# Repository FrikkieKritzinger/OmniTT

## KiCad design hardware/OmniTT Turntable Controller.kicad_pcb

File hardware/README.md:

# Hardware (KiCad 10)

KiCad project for the OmniTT controller: main board (`OmniTT Turntable Controller.kicad_pcb`),
the root schematic, and the two sub-sheets:

- `tt_control.kicad_sch`: button board (J5, ladder, shortcut buttons)
- `loconet_interface.kicad_sch`: LocoNet interface (J7, Q3, U5, R9 to R14), unpopulated in this revision

Open `OmniTT Turntable Controller.kicad_pro` in KiCad 10.

## External libraries

The design uses two custom libraries.

| Library nickname | Used for | Where it lives | Origin |
|---|---|---|---|
| `DFRobot` (symbol) and `library` (footprint) | DFRobot TB6612FNG motor driver module (U3) | In the repo: `libraries/DFRobot.kicad_sym` and `libraries/library.pretty/` | Designed by the author |
| `TTGO_T7_MINI32_V1.3` (symbol and footprint) | ESP32 D1 Mini (WROOM-32) module (U4) | Not in the repo | Downloaded footprint (SnapEDA basis), modified by the author |

`sym-lib-table` and `fp-lib-table` point KiCad at the in-repo libraries using `${KIPRJMOD}`,
so the project resolves them without any global setup.

The TTGO library isn't in the repo. Install it in KiCad from your own copy before opening
the project, or its footprint shows as missing. Its SnapEDA origin needs checking before
it's added to the repo.

Standard KiCad libraries (Resistor_THT, Capacitor_THT, Connector_PinHeader, Package_TO_SOT, and so on)
ship with KiCad and need no separate install.

## Notes

- Schematic symbols are embedded in each `.kicad_sch`, so the schematic opens without the
  symbol libraries. The PCB footprints still need them.
- Local KiCad state (`*.kicad_prl`), lock files and backups are excluded in `.gitignore`.

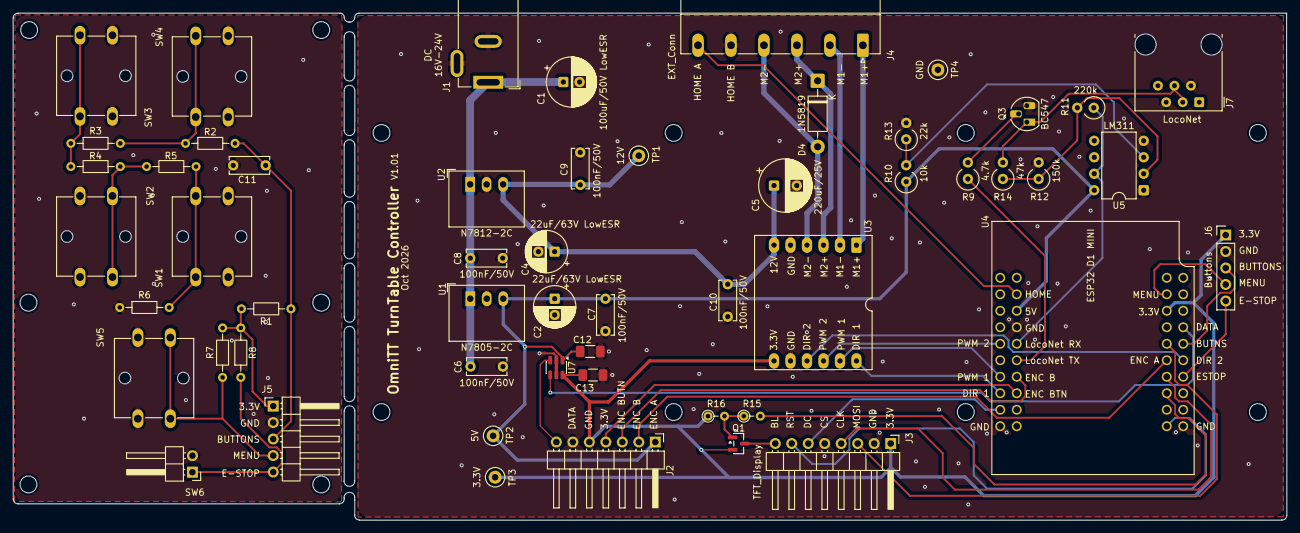
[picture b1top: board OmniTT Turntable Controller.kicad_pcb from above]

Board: 2 copper layers, 196.2 x 78.1 mm, 54 parts (0 on the bottom side), 39 nets.

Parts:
C1: 100uF/50V LowESR; CP_Radial_D7.5mm_P2.50mm
C2, C4: 22uF/63V LowESR; CP_Radial_D6.3mm_P2.50mm
C5: 220uF/25V; CP_Radial_D8.0mm_P3.50mm
C6, C7, C8, C9, C10: 100nF/50V; C_Disc_D6.0mm_W2.5mm_P5.00mm
C11: 0.1uF Cer Disc; C_Disc_D6.0mm_W2.5mm_P5.00mm
C12, C13: 100nF/25V; C_1206_3216Metric_Pad1.33x1.80mm_HandSolder
D4: 1N5819; D_DO-41_SOD81_P10.16mm_Horizontal
J1: Barrel_Jack_Switch; BarrelJack_GCT_DCJ200-10-A_Horizontal
J2: Encoder+SW; PinHeader_1x07_P2.54mm_Horizontal
J3: TFT_Display; PinHeader_1x08_P2.54mm_Horizontal
J4: EXT_Conn; PhoenixContact_MC_1,5_6-G-5.08_1x06_P5.08mm_Horizontal
J5: Buttons_01x05_Pin; PinHeader_1x05_P2.54mm_Horizontal
J6: Buttons; PinHeader_1x05_P2.54mm_Vertical
J7: LocoNet; RJ12_Amphenol_54601-x06_Horizontal
Q1: Si2301CDS; SOT-23
Q3: BC547; TO-92L_HandSolder
R1: 1k; R_Axial_DIN0204_L3.6mm_D1.6mm_P7.62mm_Horizontal
R2, R4: 430R; R_Axial_DIN0204_L3.6mm_D1.6mm_P7.62mm_Horizontal
R3: 270R; R_Axial_DIN0204_L3.6mm_D1.6mm_P7.62mm_Horizontal
R5: 680R; R_Axial_DIN0204_L3.6mm_D1.6mm_P7.62mm_Horizontal
R6: 1.3k; R_Axial_DIN0204_L3.6mm_D1.6mm_P7.62mm_Horizontal
R7, R8: 10k; R_Axial_DIN0204_L3.6mm_D1.6mm_P7.62mm_Horizontal
R9: 4.7k; R_Axial_DIN0309_L9.0mm_D3.2mm_P2.54mm_Vertical
R10: 10k; R_Axial_DIN0309_L9.0mm_D3.2mm_P2.54mm_Vertical
R11: 220k; R_Axial_DIN0309_L9.0mm_D3.2mm_P2.54mm_Vertical
R12: 150k; R_Axial_DIN0309_L9.0mm_D3.2mm_P2.54mm_Vertical
R13: 22k; R_Axial_DIN0309_L9.0mm_D3.2mm_P2.54mm_Vertical
R14: 47k; R_Axial_DIN0309_L9.0mm_D3.2mm_P2.54mm_Vertical
R15: 100R; R_Axial_DIN0204_L3.6mm_D1.6mm_P2.54mm_Vertical
R16: 10k; R_Axial_DIN0204_L3.6mm_D1.6mm_P2.54mm_Vertical
SW1: SPEED; SW_SPST_Omron_B3F-50xx
SW2: LAST EXIT; SW_SPST_Omron_B3F-50xx
SW3: PRESET B; SW_SPST_Omron_B3F-50xx
SW4: PRESET A; SW_SPST_Omron_B3F-50xx
SW5: MENU; SW_SPST_Omron_B3F-50xx
SW6: E-STOP; PinHeader_1x02_P2.54mm_Horizontal
TP1: 12V; TestPoint_Loop_D1.80mm_Drill1.0mm_Beaded
TP2: 5V; TestPoint_Loop_D1.80mm_Drill1.0mm_Beaded
TP3: 3.3V; TestPoint_Loop_D1.80mm_Drill1.0mm_Beaded
TP4: GND; TestPoint_Loop_D1.80mm_Drill1.0mm_Beaded
U1: N7805-2C; Converter_DCDC_RECOM_R-78HB-0.5_THT
U2: N7812-2C; Converter_DCDC_RECOM_R-78HB-0.5_THT
U3: DFRobot TB6612FNB Module
U4: ESP32 D1 MINI; MODULE_TTGO_T7_MINI32_V1.3
U5: LM311; DIP-8_W7.62mm
U7: SN74LVC1T45DBV; SOT-23-6

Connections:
+3.3V: C13.2, J2.5, J3.1, J5.1 (3.3V), J6.1, Q1.2 (S), R1.2, R7.2, R8.2, R16.1, TP3.1 (1_1), U3.7 (VCC), U4.P1_16 (3V3), U7.6 (VCCB)
+5V: C2.1, C7.1, C12.1, J2.1, R10.1, TP2.1 (1_1), U1.3 (VO), U4.P2_15 (5V), U5.8 (V+), U7.1 (VCCA)
+12V: C4.1, C5.1, C9.2, C10.1, TP1.1 (1_1), U2.3 (VO), U3.6 (VM(<12V))
BL: J3.8, Q1.3 (D)
BUTTONS_ADC_IN: C11.2, J5.3 (BUTTONS_ADC_IN), J6.3, R1.1, R2.2, U4.P1_11 (GPIO34)
CLK: J3.4, U4.P1_8 (GPIO18)
DIR 1: U3.12 (DIR1), U4.P2_6 (GPIO25)
DIR 2: U3.9 (DIR2), U4.P1_9 (GPIO33)
D/C: J3.6, U4.P2_4 (GPIO27)
ENCODER A: J2.2, U4.P1_10 (GPIO19)
ENCODER B: J2.3, U4.P2_7 (GPIO21)
ENCODER BUTTON: J2.4, U4.P2_5 (GPIO22)
E_STOP: J5.5 (ESTOP), J6.5, R8.1, SW6.1, U4.P1_7 (GPIO35)
GND: C1.2, C2.2, C4.2, C5.2, C6.2, C7.2, C8.1, C9.1, C10.2, C11.1, C12.2, C13.1, J1.2, J1.3, J2.6, J3.2, J3.5, J4.5 (Home_SW_A), J5.2 (GND), J6.2, J7.2, J7.5, Q3.3 (E), R6.1, R12.2, R13.2, SW1.2, SW2.2, SW3.2, SW4.2, SW5.2, SW6.2, TP4.1 (1_1), U1.2 (GND), U2.2 (GND), U3.5 (GND), U3.8 (GND), U4.P1_1 (GND1_1), U4.P2_2 (GND2_2), U4.P2_13 (GND2_13), U5.1 (GND), U5.4 (V-), U7.2 (GND), U7.5 (DIR)
HOME: J4.6 (Home_SW_B), U4.P2_17 (TDO)
LN_IN (RX): R11.1, U4.P2_11 (GPIO16), U5.7
LN_OUT (TX): R9.1, U4.P2_9 (GPIO17)
M1 +: J4.1 (Motor_1_+), U3.1 (M1+)
M1 -: J4.2 (Motor_1_-), U3.2 (M1-)
M2 +: D4.1 (K), J4.3 (Motor_2_+), U3.3 (M2+)
M2 -: D4.2 (A), J4.4 (Motor_2_-), U3.4 (M2-)
MENU: J5.4 (MENU), J6.4, R7.1, SW5.1, U4.P1_18 (TCK)
MOSI: J3.3, U4.P1_12 (GPIO23)
NEOPIXEL DATA: U4.P1_13 (TMS), U7.4 (B)
unnamed: J2.7, U7.3 (A)
unnamed: Q1.1 (G), R15.1, R16.2
unnamed: Q3.2 (B), R9.2
unnamed: J7.3, J7.4, Q3.1 (C), R14.2
unnamed: R2.1, R3.2, SW4.1
unnamed: R3.1, R4.2, SW3.1
unnamed: R4.1, R5.2, SW2.1
unnamed: R5.1, R6.2, SW1.1
unnamed: C1.1, C6.1, C8.2, J1.1, U1.1 (VI), U2.1 (VI)
unnamed: R15.2, U4.P1_6 (GPIO26)
unnamed: R11.2, R12.1, R14.1, U5.2 (+)
unnamed: R10.2, R13.1, U5.3 (-)
PWM 1: U3.11 (PMW1), U4.P2_8 (GPIO32)
PWM 2: U3.10 (PWM2), U4.P2_12 (GPIO04)
RST: J3.7, U4.P1_2 (RST)

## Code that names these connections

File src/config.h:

#ifndef CONFIG_H
#define CONFIG_H

// Hardware pins (ESP32 D1 Mini - WROOM-32 variant)
// Comments give the board silkscreen label first, then the GPIO number.
// Strapping pins in use: TDO (home sensor, pulled up at boot) only. See docs/GPIO_REFERENCE.md.

// SPI display (Waveshare 2.0" IPS, 240x320, ST7789V). CS is hard-wired low: the display is the only SPI device.
// RST is tied to the ESP32 RST line. BL is driven by PWM through a MOSFET (backlight draws about 45 mA).
#define PIN_DISPLAY_CLK   18  // label 18 (GPIO18) - SPI clock
#define PIN_DISPLAY_MOSI  23  // label 23 (GPIO23) - SPI data (DIN)
#define PIN_DISPLAY_DC    27  // label 27 (GPIO27) - Data/command
#define PIN_DISPLAY_BL    26  // label 26 (GPIO26) - Backlight PWM (via MOSFET)

// Rotary encoder (with integrated button)
#define PIN_ENCODER_A    19  // label 19 (GPIO19) - Encoder A
#define PIN_ENCODER_B    21  // label 21 (GPIO21) - Encoder B
#define PIN_ENCODER_BTN  22  // label 22 (GPIO22) - Encoder button

// Button board (external pull-ups)
#define PIN_MENU_BTN     13  // label TCK (GPIO13) - MENU
#define PIN_ESTOP        35  // label 35 (GPIO35) - Emergency STOP, normally open, active LOW (input-only, external pull-up)
#define PIN_BUTTON_LADDER 34 // label 34 (GPIO34) - Resistor ladder: PRESET A, PRESET B, LAST EXIT, SPEED (ADC1, input-only)

// Resistor ladder: series string (430, 270, 430, 680 and 1.3k ohm to GND) fed from 3.3 V through 1 kΩ,
// with a 0.1 µF filter on the ADC node. Levels in millivolts. Button assignment is set here.
#define LADDER_MV_PRESET_A  992   // Button 4: 430 Ω to GND
#define LADDER_MV_PRESET_B  1359  // Button 3: 700 Ω
#define LADDER_MV_LAST_EXIT 1755  // Button 2: 1.13 kΩ
#define LADDER_MV_SPEED     2123  // Button 1: 1.81 kΩ
#define LADDER_MV_NONE      2497  // no button: 3.11 kΩ
#define LADDER_TOLERANCE_MV  150  // reading must be within this of a level
#define LADDER_FAULT_LOW_MV  700  // below this is a fault (short to GND)

// LocoNet (later phase, not in the initial build): RX label 16 (GPIO16) and TX label 17 (GPIO17) are reserved.

// Motor (TB6612FNG channel A)
#define PIN_MOTOR_DIR1   25  // label 25 (GPIO25) - Motor direction
#define PIN_MOTOR_PWM1   32  // label 32 (GPIO32) - Motor PWM speed

// Lock solenoid (TB6612FNG channel B)
#define PIN_SOLENOID_DIR2 33 // label 33 (GPIO33) - Solenoid direction, set by jumper (see OI-12 / to-do)
#define PIN_SOLENOID_PWM2  4 // label 4 (GPIO4) - Solenoid PWM (drive high to hold open)

// Home sensor (microswitch, internal pull-up)
#define PIN_HOME_SENSOR  15  // label TDO (GPIO15) - Microswitch at home position (exit 0). Strapping pin, pulled up at boot

// Status ring (NeoPixel data)
#define PIN_STATUS_RING  14  // label TMS (GPIO14) - WS2812 data

// Motor control defaults
#define MOTOR_PWM_MAX 1023
#define MOTOR_PWM_DEFAULT 512
#define MOTOR_STEP_DURATION_MS 50  // Time between motor steps

// Display
#define DISPLAY_WIDTH 240
#define DISPLAY_HEIGHT 320

// EEPROM
// Storage backend (EEPROM emulation or NVS) to be decided in Phase 1
#define EEPROM_SIZE 4096
#define EEPROM_CONFIG_OFFSET 0
#define EEPROM_CONFIG_SIZE 256
#define EEPROM_DEFAULTS_OFFSET 256  // Factory defaults region (MNU-10/11)
#define EEPROM_CONFIG_MAGIC 0xA5C3
#define EEPROM_CONFIG_VERSION 1

// Default configuration values
#define DEFAULT_LOCONET_BASE_ADDRESS 200
#define DEFAULT_NUM_EXITS 0  // Set per turntable (CFG-03); 0 = not configured
#define DEFAULT_HOME_POSITION 0

// Wi-Fi
#define WIFI_SETUP_MODE_HOLD_TIME_MS 3000
#define WIFI_CONNECT_TIMEOUT_MS 300

// LocoNet (later phase)
#define LOCONET_STOP_BROADCAST_ENABLED 1  // Local e-stop sends to LocoNet (RUN-10..14)

#endif // CONFIG_H
